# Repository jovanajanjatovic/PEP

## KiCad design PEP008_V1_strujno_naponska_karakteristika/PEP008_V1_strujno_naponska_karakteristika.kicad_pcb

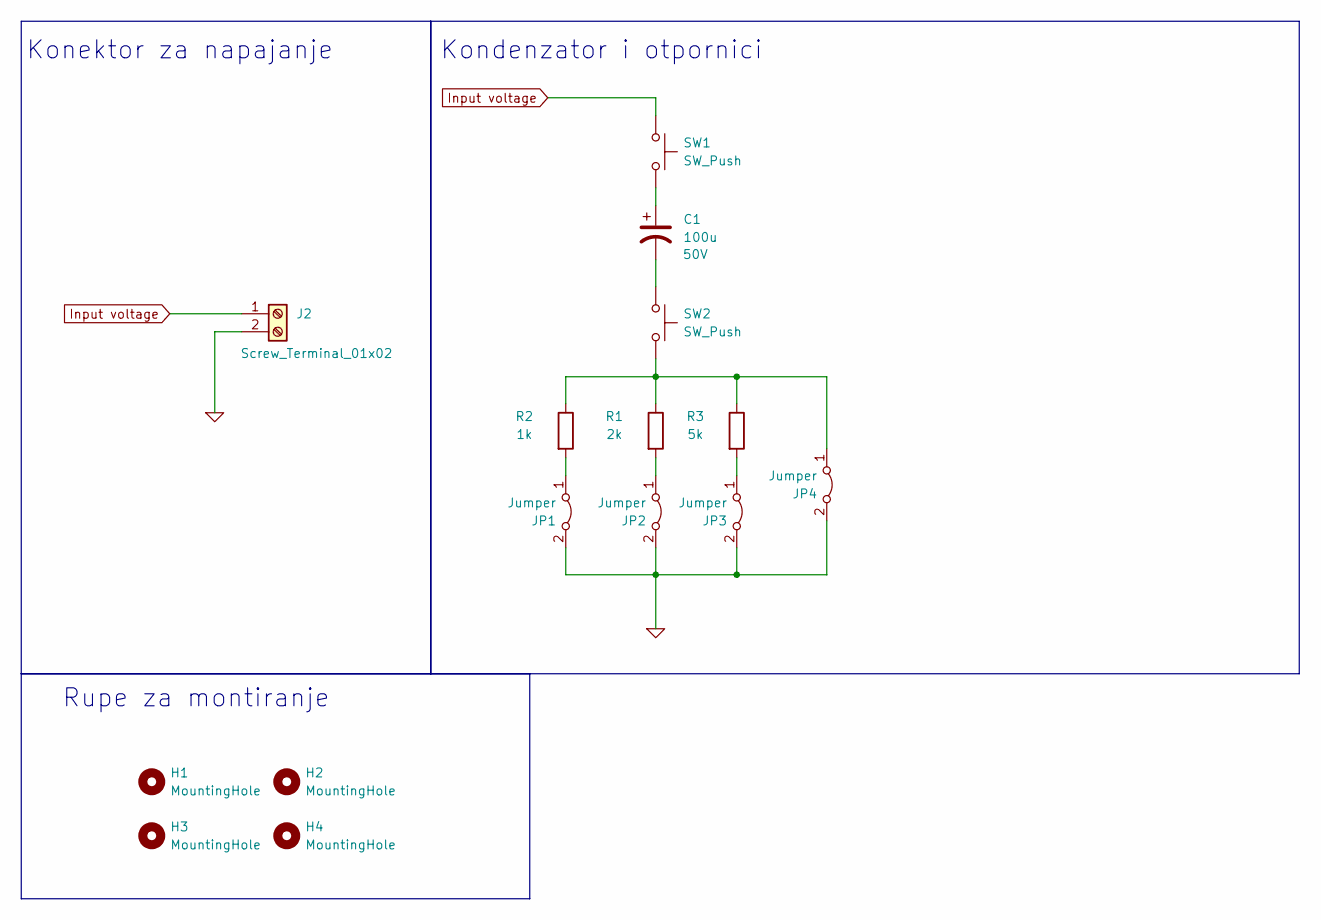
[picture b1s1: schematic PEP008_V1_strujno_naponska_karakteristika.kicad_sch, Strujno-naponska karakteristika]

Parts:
C1: 100u; CP_Radial_D8.0mm_P3.50mm; Voltage 50V
H1, H2, H3, H4: MountingHole; MountingHole_3.2mm_M3_ISO14580_Pad_TopBottom
J2: Screw_Terminal_01x02; TerminalBlock_Phoenix_MKDS-1,5-2-5.08_1x02_P5.08mm_Horizont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
JP1, JP2, JP3, JP4: Jumper; PinHeader_1x02_P2.54mm_Vertical
R1: 2k; R_1206_3216Metric_Pad1.30x1.75mm_HandSolder
R2: 1k; R_1206_3216Metric_Pad1.30x1.75mm_HandSolder
R3: 5k; R_1206_3216Metric_Pad1.30x1.75mm_HandSolder
SW1, SW2: SW_Push; SW_PUSH_6mm_H4.3mm

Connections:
0: J2.2, JP1.2 (B), JP2.2 (B), JP3.2 (B), JP4.2 (B)
Input voltage: J2.1, SW1.1
unnamed 2: C1.1, SW1.2; also elsewhere on the board
unnamed 3: C1.2, SW2.1; also elsewhere on the board
unnamed: JP1.1 (A), R2.2
unnamed: JP2.1 (A), R1.2
unnamed: JP3.1 (A), R3.2
unnamed: JP4.1 (A), R1.1, R2.1, R3.1, SW2.2

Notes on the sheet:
Rupe za montiranje
Konektor za napajanje
Kondenzator i otpornici

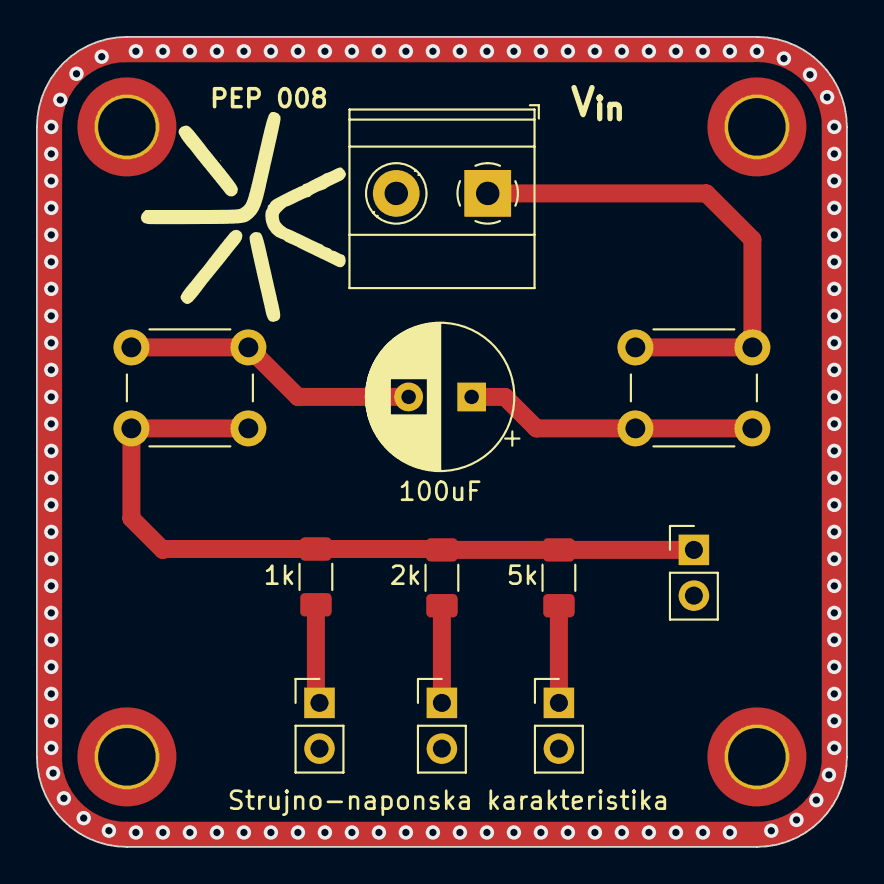
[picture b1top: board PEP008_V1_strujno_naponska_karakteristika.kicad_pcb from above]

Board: 2 copper layers, 45.0 x 45.0 mm, 15 parts (0 on the bottom side), 8 nets.

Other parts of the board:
100uF: 100u; CP_Radial_D8.0mm_P3.50mm

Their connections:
unnamed 2: 100uF.1; also elsewhere on the board
unnamed 3: 100uF.2; also elsewhere on the board

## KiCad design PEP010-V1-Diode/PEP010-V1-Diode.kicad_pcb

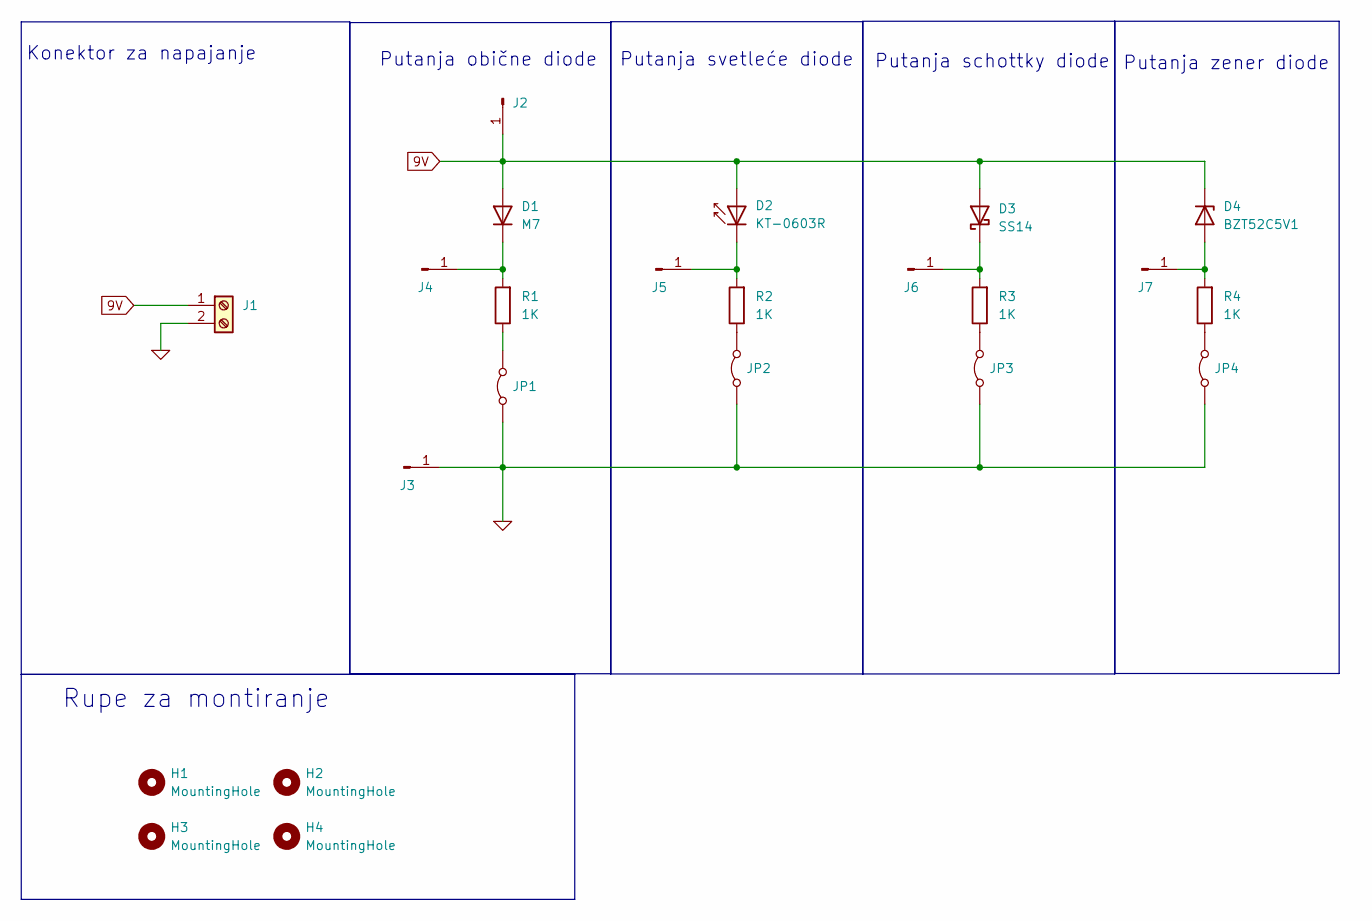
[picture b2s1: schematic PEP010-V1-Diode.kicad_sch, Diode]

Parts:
D1: M7; D_SMA; LCSC C95872
D2: KT-0603R; D_0603; LCSC C2286
D3: SS14; D_SMA; LCSC C2480
D4: BZT52C5V1; D_SOD-123; LCSC C173407
H1, H2, H3, H4: MountingHole; MountingHole_3.2mm_M3_ISO14580_Pad_TopBottom
J1: Screw_Terminal_01x02; TerminalBlock_Phoenix_MKDS-1,5-2-5.08_1x02_P5.08mm_Horizont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
J2, J3, J4, J5, J6, J7: Conn_01x01_Pin; PinHeader_1x01_P2.54mm_Vertical
JP1, JP2, JP3, JP4: Jumper_2_Bridged; PinHeader_1x02_P2.54mm_Vertical
R1, R2, R3, R4: 1K; R_1206_3216Metric; LCSC C4410

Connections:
0: J1.2, J3.1, JP1.1 (A), JP2.1 (A), JP3.1 (A), JP4.1 (A)
9V: D1.2 (A), D2.2 (A), D3.2 (A), D4.1 (K), J1.1, J2.1
unnamed: D1.1 (K), J4.1, R1.2
unnamed: D2.1 (K), J5.1, R2.2
unnamed: D3.1 (K), J6.1, R3.2
unnamed: D4.2 (A), J7.1, R4.2
unnamed: JP1.2 (B), R1.1
unnamed: JP2.2 (B), R2.1
unnamed: JP3.2 (B), R3.1
unnamed: JP4.2 (B), R4.1

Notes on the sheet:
Rupe za montiranje
Putanja svetleće diode
Konektor za napajanje
Putanja obične diode
Putanja schottky diode
Putanja zener diode

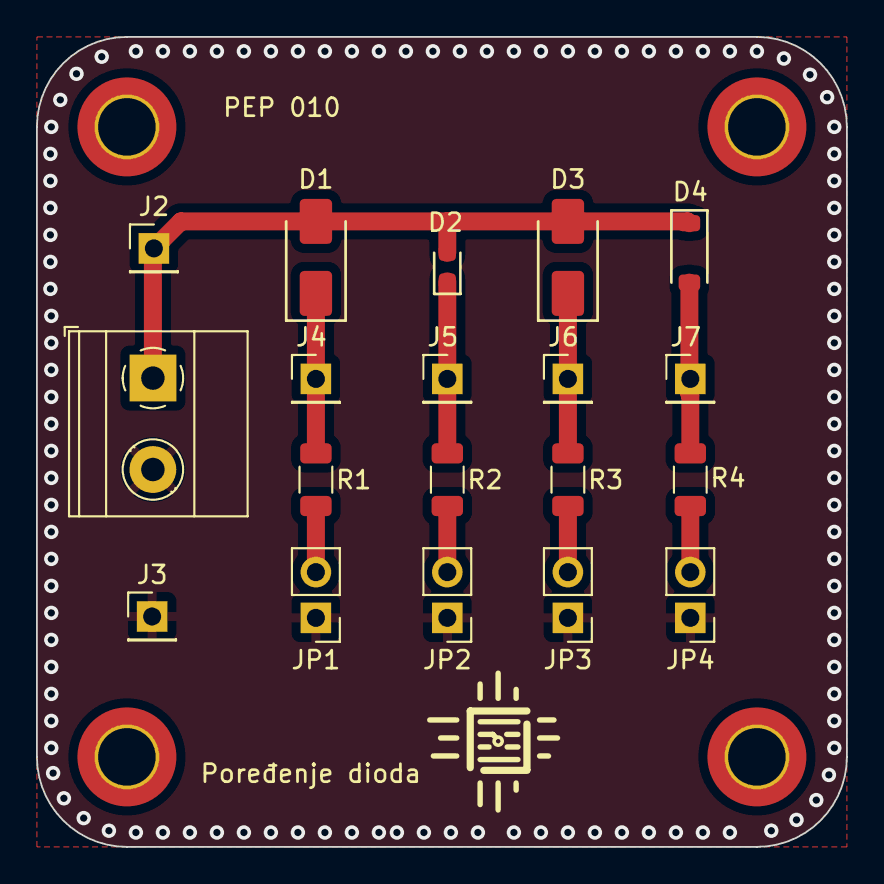
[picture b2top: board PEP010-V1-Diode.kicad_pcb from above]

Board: 2 copper layers, 45.0 x 45.0 mm, 23 parts (0 on the bottom side), 10 nets.
